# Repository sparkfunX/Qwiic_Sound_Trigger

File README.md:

# Qwiic Sound Trigger

A sound trigger which you can use on its own, or as part of your Qwiic system.

[Qwiic Sound Trigger (SPX-17979)](https://www.sparkfun.com/products/17979)

The Qwiic Sound Trigger is based on the VM1010 from Vesper Technologies and the TI PCA9536 GPIO expander.

The VM1010 is a clever little device which can be placed into a very low power "Wake On Sound" mode. When it detects a sound,
it wakes up and pulls its TRIG (D<sub>OUT</sub>) pin high. The VM1010 can then be placed into "Normal" mode by pulling the
MODE pin low; it then functions as a regular microphone. The analog microphone signal is available on the AUDIO (V<sub>OUT</sub>) pin.
All of this happens really quickly, within 50 _microseconds_ (_much_ faster than a capacitive MEMS microphone), so you don't miss
the start of the audio signal.

The noise threshold required to wake the VM1010 can be programmed via the resistance between pins GA1 and GA2. By default, the 20K
resistor on the breakout sets the noise threshold to close to the minimum (most sensitive) setting. You can increase the threshold
to maximum (least sensitive) by cutting the THRESH jumper. You can set it mid-way by adding your own resistor between breakout pins GA1 and GA2.

If you are using the VM1010 purely as a sound trigger, you need to reset it after each event by: pushing the MODE button;
pulling the MODE breakout pin low; or using the Qwiic bus to instruct the PCA9536 to pull the MODE signal low (the VM1010 MODE signal is connected to GPIO0).

You can use the TRIG (D<sub>OUT</sub>) breakout pin to generate an interrupt on your microcontroller. Or you can read (poll) its state via
the PCA9536 (the TRIG (D<sub>OUT</sub>) signal is connected to GPIO1).

There are two LEDs: one to indicate if the breakout is powered; and a second to show when a sound trigger has taken place. You can disable
either or both LEDs by cutting the LED jumpers on the back of the breakout.

As usual, the breakout includes I<sup>2</sup>C pull-up resistors. You can disable those if you need to by cutting the I2C jumpers.

The [**/Examples**](./Examples) folder contains two example sketches for the Arduino IDE:
- Example1 is a very simple example showing how to read the sound trigger TRIG signal via the PCA9536 GPIO1 pin and reset it via the MODE signal and GPIO2
- Example2 is a more complex example showing how you can capture and log the rising edge of the sound event with _nanosecond_ resolution using a ZED-F9P GNSS receiver

The [**/Utils**](./Utils) folder contains Python tools which can process the UBX TIM_TM2 data logged by Example2 and calculate the location of the sound events.

## Repository Contents
- [**/Examples**](./Examples) - Example sketches (.ino). Run these from the Arduino IDE
- [**/Utils**](./Utils) - Python tools to process the UBX TIM_TM2 data logged by Example2
- [**/Documents**](./Documents) - Datasheets etc. for both the VM1010 and PCA9536
- [**/Hardware**](./Hardware) - Eagle schematic and PCB design files
- [**LICENSE.md**](./LICENSE.md) contains the licence information

## Library

- **[SparkFun PCA9536 Arduino Library](https://github.com/sparkfun/SparkFun_PCA9536_Arduino_Library)** - Library for the TI PCA9536 4-Bit GPIO Expander

**_Your friends at SparkFun_**

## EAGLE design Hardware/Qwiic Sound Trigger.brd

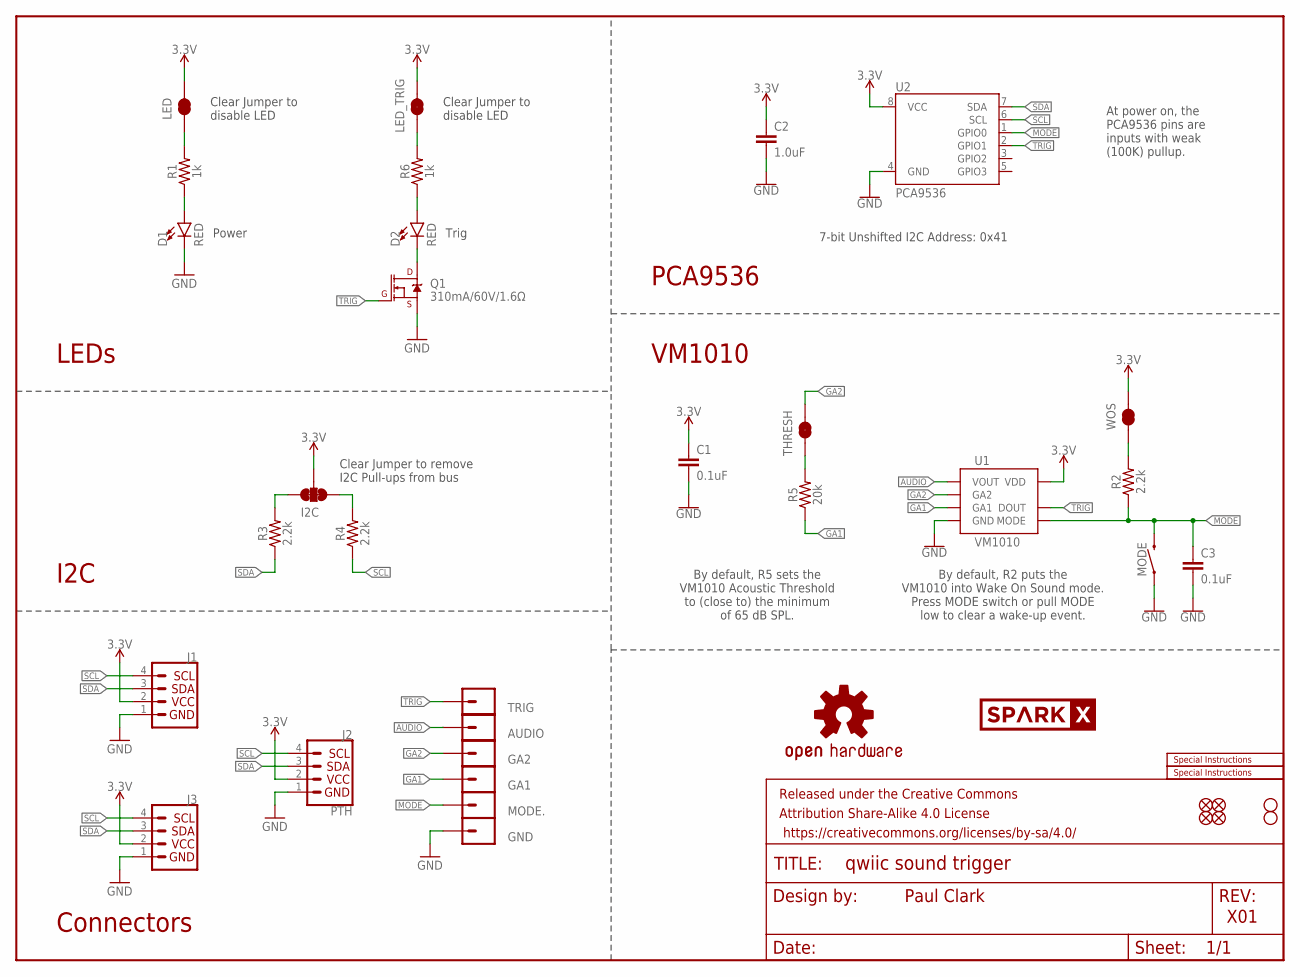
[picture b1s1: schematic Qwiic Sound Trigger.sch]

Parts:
AUDIO: CONN_01PTH_NO_SILK_YES_STOP; 1X01_NO_SILK
C1, C3: 0.1uF; 0603
C2: 1.0uF; 0603
D1, D2: RED; LED-0603
FRAME1: FRAME-LETTER; CREATIVE_COMMONS
GA1, GA2: CONN_01PTH_NO_SILK_YES_STOP; 1X01_NO_SILK
GND: CONN_01PTH_NO_SILK_YES_STOP; 1X01_NO_SILK
I2C: JUMPER-SMT_3_2-NC_TRACE_SILK; SMT-JUMPER_3_2-NC_TRACE_SILK
J1, J3: Qwiic Right Angle; JST04_1MM_RA
J2: PTH; 1X04_NO_SILK
JP1, JP2, JP5, JP6: FIDUCIAL1X2; FIDUCIAL-1X2
JP3, JP4: STAND-OFF
LED: JUMPER-SMT_2_NC_TRACE_SILK; SMT-JUMPER_2_NC_TRACE_SILK
LED_TRIG: JUMPER-SMT_2_NC_TRACE_SILK; SMT-JUMPER_2_NC_TRACE_SILK
LOGO1: OSHW-LOGOMINI; OSHW-LOGO-MINI
LOGO2: SPECIAL_INSTRUCTIONS-ORDERING; ORDERING_INSTRUCTIONS
LOGO3: SPECIAL_INSTRUCTIONS-PRODUCTION; PRODUCTION_INSTRUCTIONS
MODE: MOMENTARY-SWITCH-SPST-SMD-4.6X2.8MM; TACTILE_SWITCH_SMD_4.6X2.8MM
MODE.: CONN_01PTH_NO_SILK_YES_STOP; 1X01_NO_SILK
Q1: 310mA/60V/1.6Ω; SOT323
R1, R6: 1k; 0603
R2, R3, R4: 2.2k; 0603
R5: 20k; 0603
THRESH: JUMPER-SMT_2_NC_TRACE_SILK; SMT-JUMPER_2_NC_TRACE_SILK
TRIG: CONN_01PTH_NO_SILK_YES_STOP; 1X01_NO_SILK
U1: VM1010
U2: PCA9536; MSOP8
U$2: SPARKX-LOGO4; SPARKX-MEDIUM
WOS: JUMPER-SMT_2_NC_TRACE_SILK; SMT-JUMPER_2_NC_TRACE_SILK

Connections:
3.3V: C1.1, C2.1, I2C.2, J1.2, J2.2, J3.2, LED.2, LED_TRIG.2, U1.6 (VDD), U2.8 (VCC), WOS.2
AUDIO: AUDIO.1, U1.1 (VOUT)
GA1: GA1.1, R5.1, U1.3 (GA1)
GA2: GA2.1, THRESH.2, U1.2 (GA2)
GND: C1.2, C2.2, C3.2, D1.C, GND.1, J1.1, J2.1, J3.1, MODE.1, MODE.2 (1), Q1.2 (S), U1.4 (GND), U1.8 (GND), U2.4 (GND)
MODE: C3.1, MODE.3 (2), MODE.4 (2), MODE..1, R2.1, U1.5 (MODE), U2.1 (GPIO0)
unnamed: I2C.1, R4.2
unnamed: I2C.3, R3.2
unnamed: D1.A, R1.1
unnamed: LED.1, R1.2
unnamed: R2.2, WOS.1
unnamed: R5.2, THRESH.1
unnamed: D2.A, R6.1
unnamed: LED_TRIG.1, R6.2
unnamed: D2.C, Q1.3 (D)
SCL: J1.4, J2.4, J3.4, R4.1, U2.6 (SCL)
SDA: J1.3, J2.3, J3.3, R3.1, U2.7 (SDA)
TRIG: Q1.1 (G), TRIG.1, U1.7 (DOUT), U2.2 (GPIO1)

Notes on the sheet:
Paul Clark
X01
Clear Jumper to remove I2C Pull-ups from bus
Power
7-bit Unshifted I2C Address: 0x41
Connectors
At power on, the PCA9536 pins are inputs with weak (100K) pullup.
Clear Jumper to disable LED
LEDs
I2C
PCA9536
VM1010
By default, R2 puts the VM1010 into Wake On Sound mode. Press MODE switch or pull MODE low to clear a wake-up event.
By default, R5 sets the VM1010 Acoustic Threshold to (close to) the minimum of 65 dB SPL.
Trig

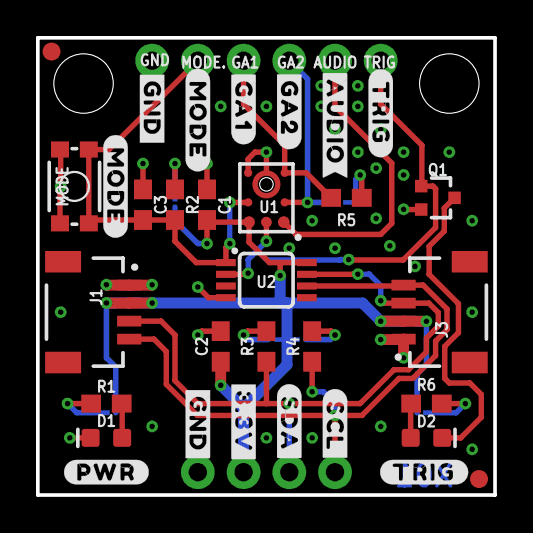
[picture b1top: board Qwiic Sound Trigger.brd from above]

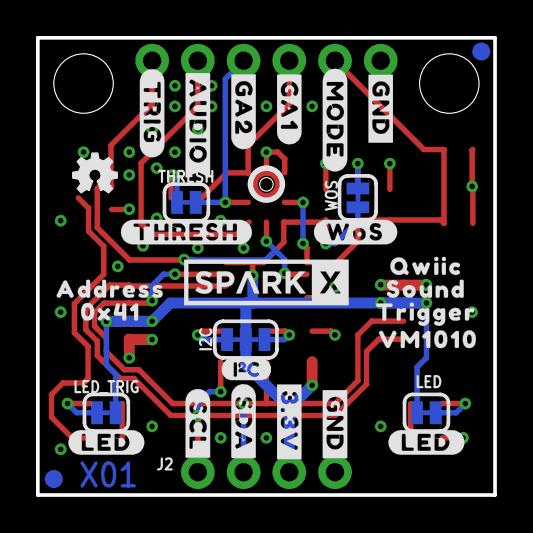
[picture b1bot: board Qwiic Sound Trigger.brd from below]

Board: 2 copper layers, 25.4 x 25.4 mm, 74 parts (31 on the bottom side), 18 nets.

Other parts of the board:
U$1, U$3: #GA1#0
U$4, U$5: #GA2#0
U$6, U$7: #AUDIO#0
U$8, U$9, U$25: #MODE#0
U$10: I_SUPER2_C-()-03
U$11, U$12, U$35: #TRIG#0
U$13: #PWR#0
U$14, U$36: #LED#0
U$15: #THRESH#0
U$16: #WOS#0
U$17, U$18, U$38, U$39: #GND#0
U$19, U$20: #3#3V#0
U$21, U$22: #SDA#0
U$23, U$24: #SCL#0
U$29: QWIIC0
U$30: SOUND0
U$31: TRIGGER0
U$32: VM10100
U$33: ADDRESS0
U$34: 0X410

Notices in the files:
parts and their libraries:
SparkFun-Resistors: Licensing: Creative Commons ShareAlike 4.0 International - https://creativecommons.org/licenses/by-sa/4.0
SparkFun-Aesthetics: Released under the Creative Commons Attribution Share-Alike 4.0 License
SparkFun-Aesthetics: https://creativecommons.org/licenses/by-sa/4.0
